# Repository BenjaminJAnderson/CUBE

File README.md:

# CUBE

CUBE is a miniature, six-faced OLED display cube built from a stack of custom interconnected PCBs. The current design combines an ESP32-S2 motherboard, five further display boards, a magnet-held 3D-printed frame and bring-up firmware for SPI displays and motion sensing.

## Overview

CUBE is a handheld, self-contained display object rather than a conventional LED matrix. Each of its six faces carries a 1.5-inch, 128×128 RGB OLED module driven by an SSD1351 controller, giving 98,304 addressable pixels across the cube. The aim is to make a small object whose faces can show independent graphics and respond to movement, while remaining easy to open, charge and repair.

The project began in December 2021 after seeing Greg Davill's [miniature LED cube](https://gregdavill.com/blog/2020/6/13/miniature-3456x-led-cube) and Pol Pla's research on [Display Blocks](https://dam-prod.media.mit.edu/x/files/sites/default/files/TEI_DisplayBlocks_CameraReady_lite.pdf). Both demonstrated the appeal of a compact, tactile display device. CUBE takes that idea in a different direction: instead of an FPGA and an LED matrix, it uses a microcontroller, six square OLED modules and a modular PCB-and-frame construction.

**Status:** design-stage prototype. The repository records work from December 2021 to May 2022. It contains the electrical and mechanical design files, photographs of a fabricated motherboard and several printed frame prototypes, and display and IMU bring-up sketches. The final assembled cube and an integrated application firmware are not present.

## Features

- **Six active faces:** one 128×128 RGB OLED on the motherboard and one on each of the five display boards.
- **Shared SPI display bus:** all six SSD1351 displays share clock, data and data/command lines, with a separate chip-select line for each face.
- **Daisy-chained construction:** 20-way, 0.5 mm pitch flat flexible cables carry power and SPI between boards, allowing the cube to be unfolded for assembly and servicing.
- **ESP32-S2 motherboard:** native USB, external-antenna module footprint, ICM-20602 six-axis IMU, USB-C input, LiPo charger with load sharing, 3.3 V regulation and a 13 V boost converter for the OLEDs.
- **Modular display boards:** D2–D6 each carry one display, two FFC connectors and the necessary decoupling and termination. The repeated design allows a single side to be revised independently later.
- **Magnet-held frame:** FreeCAD models and STEP/STL exports for the enclosure, using 3 mm neodymium magnets to join printed panels.
- **Bring-up software:** Arduino sketches that test one display at a time up to six displays, exercise the Adafruit GFX drawing primitives, and demonstrate IMU orientation output.

## Technologies

- **KiCad:** schematic capture, PCB layout and fabrication outputs. D1 uses the KiCad 6 project format; D2–D6 use the earlier `.sch` and `.pro` format.
- **ESP32-S2:** the ESP32-S2-MINI-1U supplies the processing, Wi-Fi, native USB and external-antenna option.
- **SSD1351 and Adafruit GFX:** display driver and graphics library used by the OLED modules and test sketches.
- **C/C++ with the Arduino framework:** firmware bring-up sketches for the displays and IMU.
- **FreeCAD:** mechanical design of the frame, including the panel and magnet layouts.
- **Blender:** rendered presentation of the assembled cube.
- **JLCPCB:** SLA 3D printing service used for the individual frame panels.

## Gallery

*The assembled motherboard, showing the ESP32-S2 module, USB-C connector, battery connector, FFC connector and power circuitry.*

*Motherboard schematic sheets covering the 13 V and 3.3 V supplies, battery management, USB input, IMU, display interface and ESP32-S2.*

*Mechanical reference for the 1.5-inch, 128×128 RGB OLED module, including its active area, bezel and FFC tail.*

*Two frame halves with the PCB assembly test-fitted inside.*

*An early FDM-printed frame, printed flat and folded like origami to avoid overhangs.*

*Individual SLA-printed panels with magnet pockets, produced through JLCPCB's 3D printing service.*

*A PCB and display test-fitted into a printed frame panel.*

## Technical Details

### System architecture

CUBE is built from six boards arranged as the faces of a cube. D1 is the motherboard and also carries one display. D2–D6 are display boards with the same electrical function: each accepts the incoming bus, drives one OLED and passes the bus to the next face. The boards are approximately 38 mm across and use two copper layers. The FreeCAD frame envelope is approximately 52 mm cubed.

The interconnect is a 20-way, 0.5 mm pitch FFC bus. It carries the shared SPI clock and data lines, the data/command line, 3.3 V, the 13 V OLED supply, ground and the chip-select lines that have not yet been consumed. D1 uses one select locally and forwards five to D2. Each subsequent board consumes one select and forwards the remainder, so the number of active select lines decreases along the chain until, in the intended design, D6 receives the final line. Because every display has its own chip-select, the microcontroller can update one face without disturbing the others.

### Motherboard

The motherboard is built around an ESP32-S2-MINI-1U. The module's native USB interface removes the need for a separate USB-to-UART bridge, reducing component count and board area. The 1U variant was selected for its external-antenna option.

The main subsystems are:

- **Power input and battery management:** a USB-C receptacle feeds a MCP73831 LiPo charger. A P-channel MOSFET and Schottky diode provide load sharing between USB and battery power. A 2-pin JST PH connector accepts the battery.
- **Regulation:** a MIC5353 provides the 3.3 V rail, while a FAN5331 boost converter generates the 13 V bias required by the OLED modules.
- **Sensing:** an ICM-20602 accelerometer and gyroscope share the SPI bus and provide an interrupt output.
- **Display interface:** a 20-pin FFC connector distributes the bus to the first display board. The motherboard also carries one SSD1351 display module on its top face.
- **Control and status:** a two-way DIP switch provides boot and reset control, and green LEDs indicate power and charger status.

### Display boards

D2–D6 share the same basic layout and component set, although the chip-select wiring changes along the chain. Each board contains one 1.5-inch 128×128 SSD1351 OLED module, two 20-pin FFC connectors for the daisy chain, decoupling capacitors and series components for the display signals. There is no local microcontroller; all rendering is performed by the ESP32-S2 and sent over the shared bus.

The D6 directory currently contains copies of the D5 files, including the D5 chip-select assignment. This is a known naming and versioning artefact: D6 is intended to be the sixth display face, and the duplicate was left in place so that a single side could be modified later without changing the other four. Before D6 can act as the sixth face, its netlist needs to be changed to consume only `Display6_CS`.

### Mechanical design

The enclosure was developed in FreeCAD and exported as STEP and STL files. The frame is approximately 52 mm cubed and uses 3 mm neodymium magnets to hold its sections together so that the cube can be opened for charging or repair. The repository includes the FreeCAD source, the six wall panels, a compound assembly and several earlier design iterations in `Hardware/Frame/OLD`.

Three fabrication approaches were explored:

1. **FDM-printed folded frame:** the panels were printed flat in ABS and folded like origami. This avoided overhangs and produced a smooth outer surface, but the print quality and tolerances were not good enough for a finished object.
2. **Single-piece SLA lid:** an SLA print gave a better surface finish, but the material was brittle and chipped during support removal. Placing PCBs into a frame with five connected panels was also difficult.
3. **Individual magnet panels:** each panel was printed separately through JLCPCB's SLA service, allowing the PCBs and displays to be fitted easily. The finish was the best of the three, but the resulting frame was fragile when pressure was applied to opposite corners, and gluing the many magnets was slow and error-prone.

The design direction recorded in the project notes is a final frame made from two evenly sized three-sided sections, printed in SLA, with improved magnet pockets. Keeping each section to three sides makes assembly easier while still allowing the cube to be opened.

### Firmware and bring-up

The software is a collection of Arduino sketches rather than a finished application. The sequence in `Software/Display/Testing` progresses from a single display to test routines for all six faces. `1_Display_SW` initialises one display, and the later sketches add calls for more faces. The progression is not fully consistent: `3_Display_SW` initialises OLED4 but not OLED3, while `5_Display_SW` and `6_Display_SW` call drawing routines on the fifth and sixth displays without calling `begin()` on those objects. The sketches use software SPI with the following pins:

| Signal | GPIO |
| --- | --- |
| SCLK | 36 |
| MOSI | 35 |
| DC | 5 |
| CS 1 | 6 |
| CS 2 | 12 |
| CS 3 | 14 |
| CS 4 | 18 |
| CS 5 | 17 |
| CS 6 | 11 |

The display sketches use the Adafruit GFX drawing API and the Adafruit SSD1351 driver. The vendored driver files in `Software/Display/lib` have been renamed to `Multi_SSD1351`, but the source still includes `Adafruit_SSD1351.h`; the upstream Adafruit SSD1351 library should therefore be installed when building the sketches.

The IMU sketches in `Software/IMU` use an MPU6050 and Jeff Rowberg's DMP library over I2C. They print yaw, pitch and roll over serial for orientation experiments, but they do not drive the ICM-20602 fitted to the motherboard. An ICM-20602 SPI driver and the integration between sensing, rendering and power management remain to be written.

## Challenges and Solutions

### Driving six displays from one bus

Six displays could not each have a dedicated SPI peripheral, and duplicating the bus would have added wiring and pins. The chosen approach shares clock, data and data/command lines while giving every display its own chip-select. Each board consumes one select line and passes the unused lines to the next board, so the ESP32-S2 can still address any face individually without carrying all six selects to the end of the chain. The staged one-to-six test sketches provide an incremental validation path for this arrangement.

### Sourcing a suitable square display

Small, high-resolution square OLED modules are uncommon. The available 1.5-inch 128×128 SSD1351 modules have relatively large bezels, which limits the visible area of each face. The design accepts this trade-off because the modules are readily available, have an integrated controller and use a simple SPI interface. Smaller square OLEDs may become easier to source as the VR and wearable markets grow.

### Producing a repeatable frame

Each frame process exposed a different limitation: FDM printing gave poor surface finish and tolerances, SLA printing was brittle and difficult to clean up, and individual magnet panels were fragile under diagonal loads. The current design direction is two three-sided SLA sections with improved magnet pockets, balancing print quality, ease of assembly and serviceability. The prototype frames in the repository are development iterations, not the final enclosure.

### Reducing component count

An early constraint was fitting the electronics into a small cube. The ESP32-S2's native USB removed the USB-to-UART bridge and its associated circuitry, and the ESP32-S2-MINI-1U provided the processing and wireless capability in a small module. The remaining power path was kept modular: USB-C input, a LiPo charger with load sharing, a 3.3 V rail and a dedicated 13 V boost for the displays.

## Results and Validation

The repository contains evidence of the following work:

- A fabricated D1 motherboard, photographed and shown test-fitted in a frame assembly.
- KiCad schematics and PCB layouts for the motherboard and display boards.
- Printed frame prototypes, including folded FDM frames, SLA panels and a PCB test fit.
- Staged display sketches that progress from one display to calls for six faces and exercise drawing primitives.
- An IMU orientation sketch using the MPU6050 DMP library.

There is no automated test suite, no captured frame-rate or power-consumption measurements, and no integrated application firmware in this repository. The final cube has not been assembled from the final frame design.

Known limitations:

- D6 duplicates the D5 hardware files, including the D5 chip-select wiring, and is not independently versioned.
- Several sketches omit `begin()` calls: `3_Display_SW` does not initialise OLED3, and `5_Display_SW` and `6_Display_SW` do not initialise the fifth and sixth display objects.
- The vendored SSD1351 driver is renamed but retains the upstream include name.
- The IMU sketch targets the MPU6050, while the motherboard uses the ICM-20602.
- The final two-part SLA frame and the integrated firmware are still outstanding.

## Getting Started

### Prerequisites

- KiCad 6 or newer to open the D1 project; the D2–D6 boards use the older KiCad `.sch` and `.pro` formats.
- FreeCAD to edit the enclosure source and export STEP or STL files.
- Arduino IDE or an equivalent Arduino toolchain with the ESP32 board support package for the firmware sketches.
- Adafruit GFX and Adafruit SSD1351 libraries for the display sketches.
- Jeff Rowberg's MPU6050 library for the IMU demonstration.
- Blender if you want to open the presentation render.
- For a physical build: six 1.5-inch 128×128 SSD1351 OLED modules, 20-way 0.5 mm FFC cables and connectors, a compatible LiPo battery, 3 mm neodymium magnets and the printed frame parts.

### Opening the hardware design

Open `Hardware/PCB/D1(Motherboard)/D1(Motherboard).kicad_pro` in KiCad for the motherboard. The display boards are in `Hardware/PCB/D2` through `Hardware/PCB/D6`; D6 contains a copy of the D5 project.

The schematic and layout can also be viewed online through [CADLAB.io](https://cadlab.io/project/25014).

### Running the firmware

1. Install the ESP32 board support package and the Adafruit GFX and Adafruit SSD1351 libraries in the Arduino IDE.
2. Open the desired sketch under `Software/Display/Testing`. Start with `1_Display_SW` for a single display, then move up to `6_Display_SW`.
3. Select the ESP32-S2 board that matches the module on the motherboard.
4. Check the pin definitions at the top of the sketch against the board revision before uploading. The pin assignments above reflect the test sketches, not a separate board definition.
5. Add any missing `begin()` calls (for example, OLED3 in `3_Display_SW`, and OLED5 and OLED6 in the later sketches).
6. Open the Serial Monitor to see the display initialisation and test output.

For the IMU experiment, open `Software/IMU/DMP_CodeESP32/DMP_CodeESP32.ino`, install the MPU6050 library and connect an MPU6050 over I2C. This sketch is an experiment for the MPU6050 and is not a driver for the ICM-20602 on the motherboard.

### Frame and renders

The editable frame source is `Hardware/Frame/Frame.FCStd`. Exports include `Frame-Walls.step`, `Frame-Left.step`, `Frame-Compound002.step` and `Frame-Walls.stl`. Earlier frame versions are kept in `Hardware/Frame/OLD`.

The Blender presentation file is `Renders/Blender/Cube Render.blend`.

## Project Structure

```text
CUBE/
├── Hardware/
│   ├── PCB/
│   │   ├── D1(Motherboard)/    # Motherboard, power, IMU and display interface
│   │   ├── D2/                 # Display board
│   │   ├── D3/                 # Display board
│   │   ├── D4/                 # Display board
│   │   ├── D5/                 # Display board
│   │   └── D6/                 # Sixth display face; currently a copy of D5
│   └── Frame/                  # FreeCAD source, STEP exports and STL files
├── Renders/
│   ├── Blender/                # Blender presentation scene
│   ├── CubeDesign.png          # High-resolution render
│   └── Test.png                # Render
├── Software/
│   ├── Display/                # SSD1351 libraries, examples and bring-up tests
│   └── IMU/                    # MPU6050 DMP experiments
├── docs/images/                # README images
├── LICENSE
└── README.md
```

## Roadmap

- [ ] Finalise the enclosure as two three-sided SLA-printed sections with improved magnet pockets.
- [ ] Assemble a complete six-face cube from the final frame and boards.
- [ ] Write and document integrated application firmware for rendering, motion sensing and power management.
- [ ] Add an ICM-20602 SPI driver and connect it to the display application.
- [ ] Allow individual display-board revisions for each face; D6 remains a duplicate for now.

## Credits and Licensing

The project source and design files are released under the [MIT License](LICENSE), copyright 2022 Benjamin J Anderson.

Third-party material:

- The display driver and graphics code derive from Adafruit's SSD1351 and GFX libraries, which are distributed under the BSD licence. The original SSD1351 library and its licence are included in `Software/Display/Resources/Adafruit-SSD1351-library-1.1.0`.
- The IMU sketches depend on Jeff Rowberg's I2Cdevlib MPU6050 library, which is not bundled in this repository.
- Reference sketches in `Software/Display/Resources` include material from the Rotatey_Balls project, distributed under the MIT licence.
- Component datasheets, antenna documentation and vendor reference designs in `Hardware/PCB/D1(Motherboard)/Resources` remain subject to their publishers' terms.
- Design inspiration: Greg Davill's miniature LED cube and Pol Pla's Display Blocks research, linked in the Overview.

The project is also indexed on [CADLAB.io](https://cadlab.io/project/25014).

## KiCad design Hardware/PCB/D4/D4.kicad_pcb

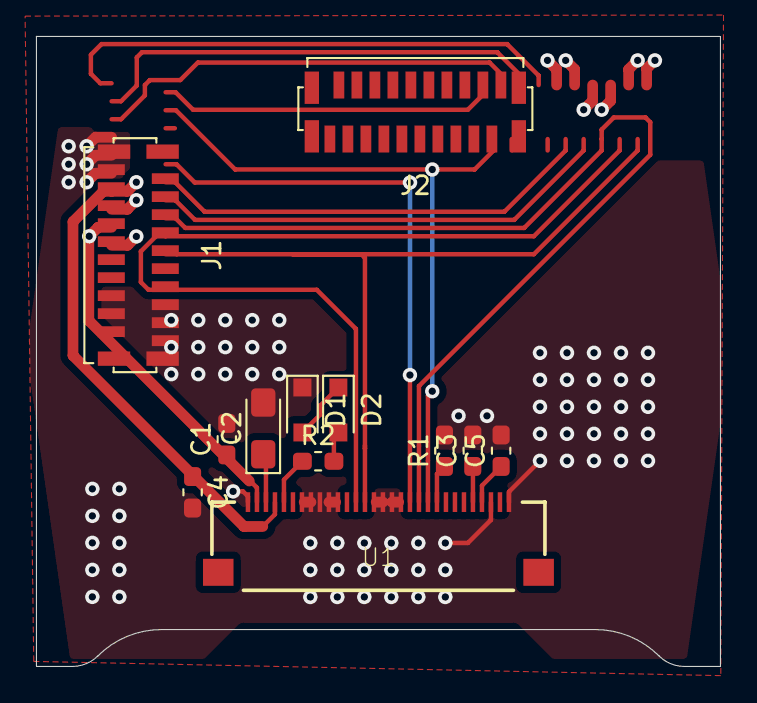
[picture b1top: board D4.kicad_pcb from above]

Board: 2 copper layers, 38.0 x 35.0 mm, 12 parts (0 on the bottom side), 21 nets.

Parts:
C1, C5: 10u; C_0603_1608Metric_Pad1.05x0.95mm_HandSolder
C2: 4.7u; CP_EIA-3216-18_Kemet-A_Pad1.58x1.35mm_HandSolder
C3: 0.1u; C_0603_1608Metric_Pad1.05x0.95mm_HandSolder
C4: 1u; C_0603_1608Metric_Pad1.05x0.95mm_HandSolder
D1, D2: 1N4148; D_SOD-323_HandSoldering
J1, J2: Conn_01x20_Female; FH12-20S-0.5SVA
R1: 560k; R_0603_1608Metric_Pad1.05x0.95mm_HandSolder
R2: 50R; R_0603_1608Metric_Pad1.05x0.95mm_HandSolder
U1: 4DOLED-282815; FPC_XF2M-3015-1A

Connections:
13V: C1.1, J1.17, J1.19, J2.1, J2.3, U1.2
+3V3: C4.1, J1.13, J1.15, J2.5, J2.7, U1.4
CLK: J1.20, J2.2, U1.14
DC: J1.16, J2.6, U1.20
Display4_CS: J1.10, U1.19
Display5_CS: J1.12, J2.10
Display6_CS: J1.14, J2.8
EN: J1.5, J2.17
GND: C1.2, C2.2, C3.2, C4.2, C5.2, D1.1, J1.7, J1.9, J1.11, J2.9, J2.11, R1.2, U1.1, U1.7, U1.8, U1.9, U1.10, U1.11, U1.15, U1.16, U1.17, U1.18, U1.28, U1.30
IO0: J1.3, J2.15
MOSI: J1.18, J2.4, U1.13
unnamed: C2.1, U1.3
unnamed: C3.1, U1.26
unnamed: C5.1, U1.27
unnamed: D1.2, D2.1
unnamed: D2.2, R2.2
unnamed: R1.1, U1.22
unnamed: R2.1, U1.5
RST: J1.4, J2.18, U1.21
RXD: J1.1, J2.13
TXD: J1.2, J2.19

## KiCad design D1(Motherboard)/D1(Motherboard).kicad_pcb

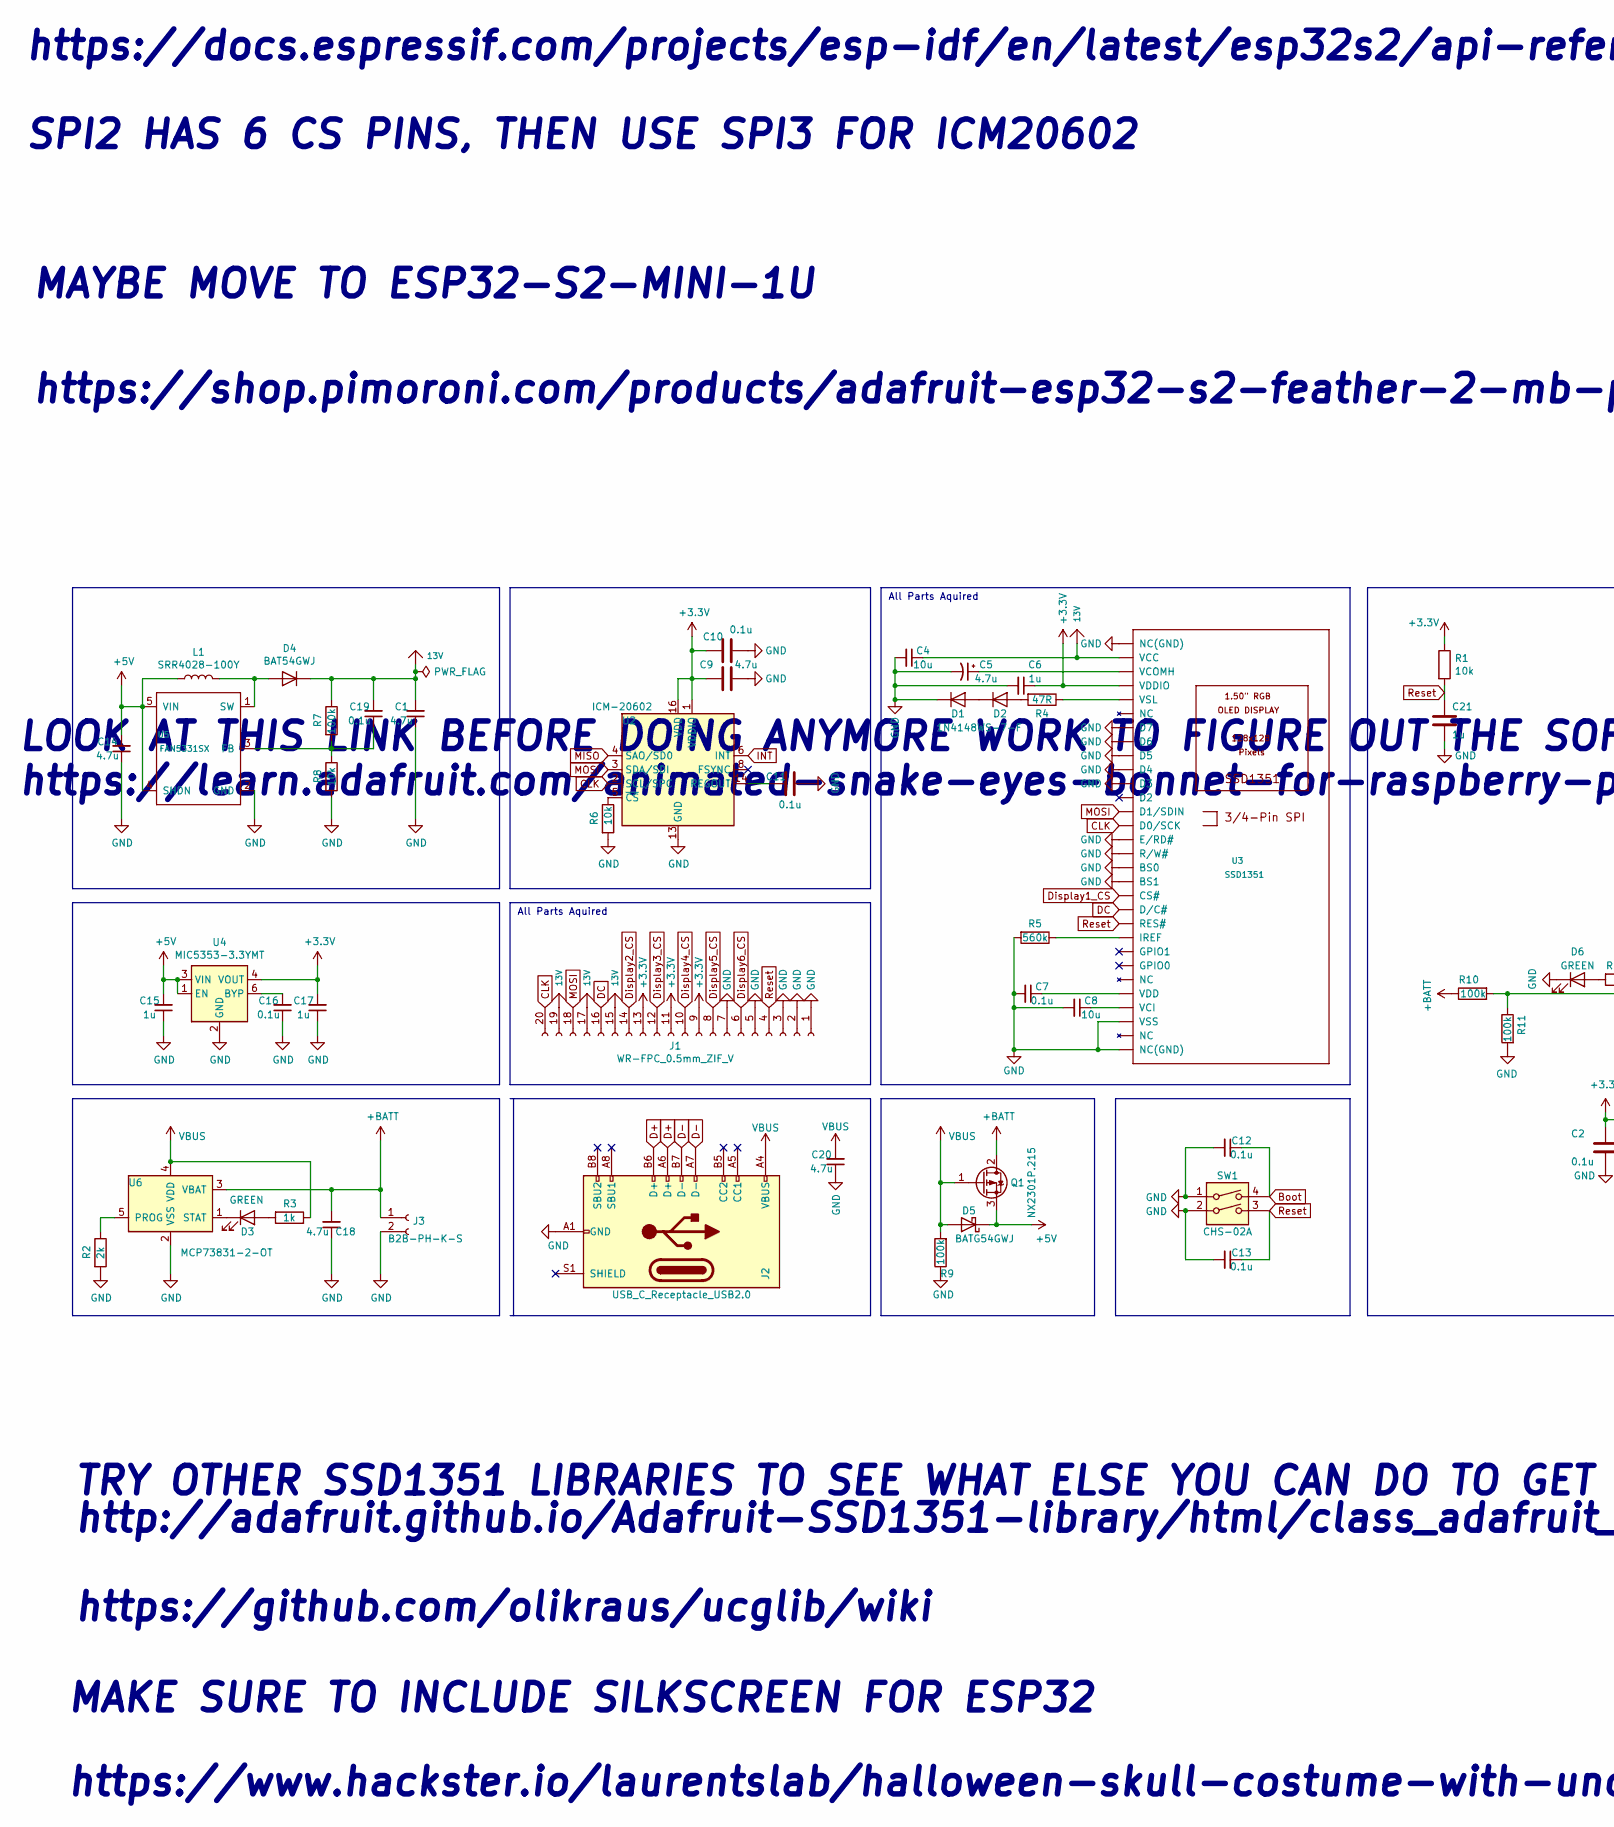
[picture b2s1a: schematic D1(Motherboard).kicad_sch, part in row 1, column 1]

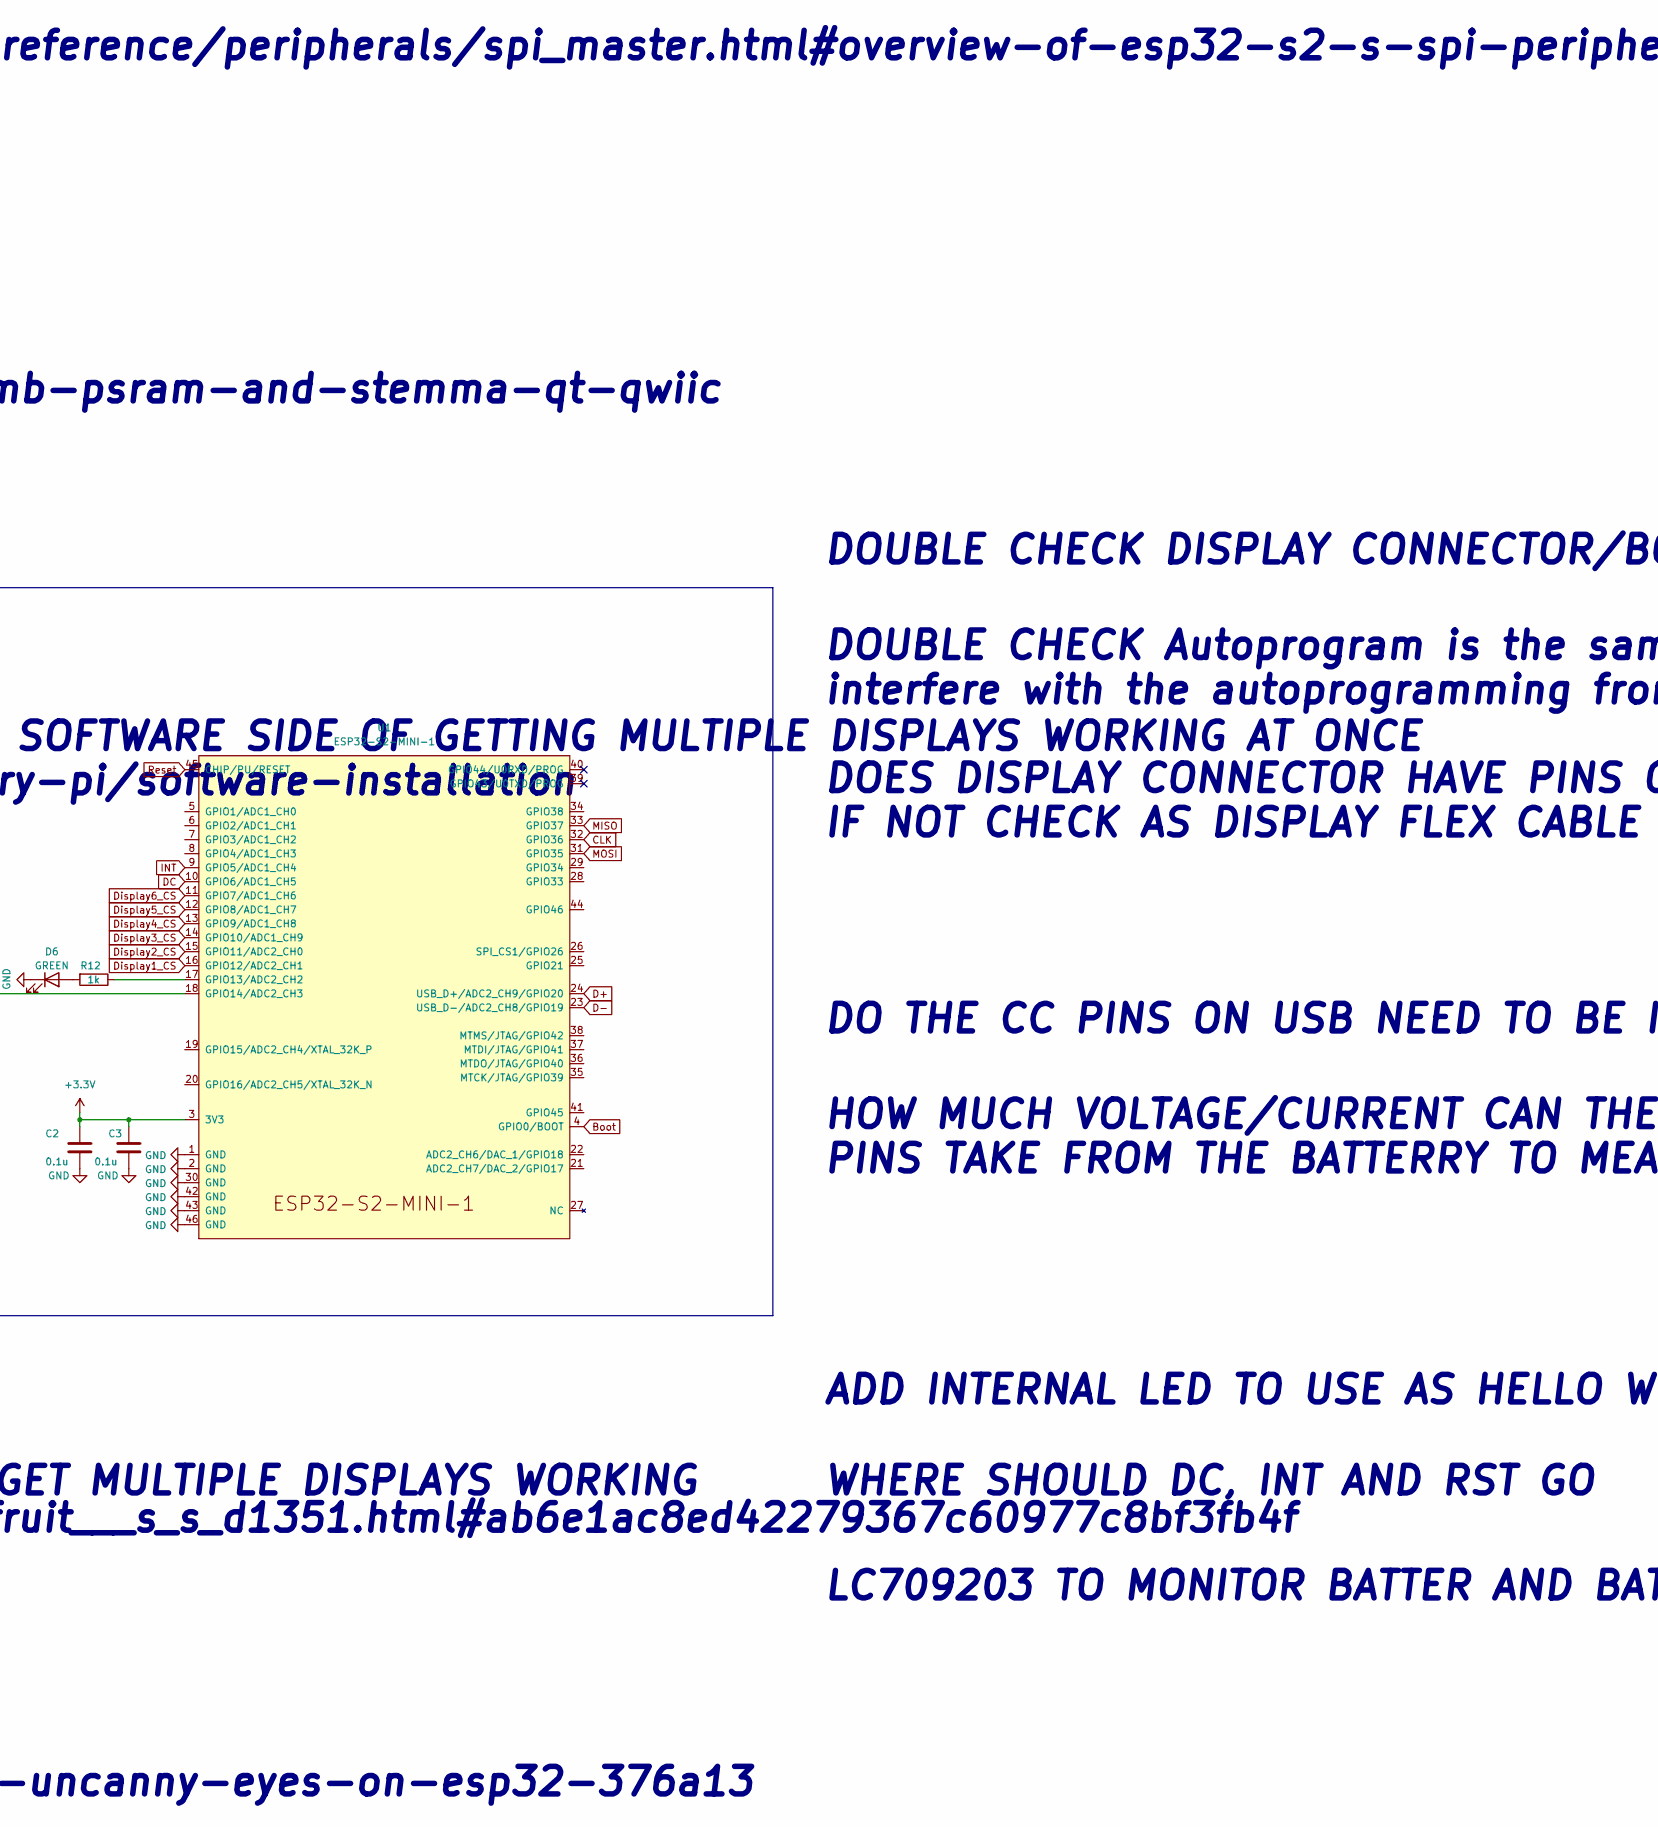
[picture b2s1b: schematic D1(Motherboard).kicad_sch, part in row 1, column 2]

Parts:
C1, C9, C14, C18, C20: 4.7u; C_0603_1608Metric
C2, C3, C7, C10, C11, C12, C13, C16, C19: 0.1u; C_0603_1608Metric
C4, C8: 10u; C_0603_1608Metric
C5: 4.7u; CP_EIA-3216-18_Kemet-A
C6, C15, C17, C21: 1u; C_0603_1608Metric
D1, D2: 1N4148WS-7-F; D_SOD-323
D3, D6: GREEN; LED_0603_1608Metric
D4: BAT54GWJ; D_SOD-123
D5: BATG54GWJ; D_SOD-123
J1: WR-FPC_0.5mm_ZIF_V; WR-FPC_0.50_SMT_ZIF_V
J2: USB_C_Receptacle_USB2.0; GCT_USB4120-03-C
J3: B2B-PH-K-S; JST_PH_B2B-PH-K_1x02_P2.00mm_Vertical
L1: SRR4028-100Y; L_Bourns-SRN4028
Q1: NX2301P.215; SOT-23
R1, R6, R8: 10k; R_0603_1608Metric
R2: 2k; R_0603_1608Metric
R3, R12: 1k; R_0603_1608Metric
R4: 47R; R_0603_1608Metric
R5: 560k; R_0603_1608Metric
R7, R9, R10, R11: 100k; R_0603_1608Metric
SW1: CHS-02A; SW_DIP_SPSTx02_Slide_Copal_CHS-02A_W5.08mm_P1.27mm_JPin
U1: ESP32-S2-MINI-1; ESP32-S2-MINI-1U
U2: ICM-20602; LGA-16_3x3mm_P0.5mm_LayoutBorder3x5y
U3: SSD1351; WR-FPC_0.5mm_ZIF_H
U4: MIC5353-3.3YMT; MLF-6-1EP_1.6x1.6mm_P0.5mm_EP0.5x1.26mm
U5: FAN5331SX; SOT-23-5
U6: MCP73831-2-OT; SOT-23-5

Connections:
13V: C1.2, C4.1, C19.2, D4.1 (K), J1.15, J1.17, J1.19, R7.1, U3.2 (VCC)
+3V3: C2.1, C3.1, C6.1, C9.2, C10.2, C17.2, J1.9, J1.11, J1.13, R1.1, U1.3 (3V3), U2.1 (VDDIO), U2.16 (VDD), U3.4 (VDDIO), U4.4 (VOUT)
+5V: C14.2, C15.2, D5.1 (K), L1.1, Q1.3 (S), U4.1 (EN), U4.3 (VIN), U5.4 (SHDN), U5.5 (VIN)
+BATT: C18.2, J3.1, Q1.2 (D), R10.1, U6.3 (VBAT)
Boot: C12.1, SW1.4, U1.4 (GPIO0/BOOT)
CLK: J1.20, U1.32 (GPIO36), U2.2 (SCL/SPC), U3.14 (D0/SCK)
D+: J2.A6 (D+), J2.B6 (D+), U1.24 (USB_D+/ADC2_CH9/GPIO20)
D-: J2.A7 (D-), J2.B7 (D-), U1.23 (USB_D-/ADC2_CH8/GPIO19)
DC: J1.16, U1.10 (GPIO6/ADC1_CH5), U3.20 (D/C#)
Display1_CS: U1.16 (GPIO12/ADC2_CH1), U3.19 (CS#)
Display2_CS: J1.14, U1.15 (GPIO11/ADC2_CH0)
Display3_CS: J1.12, U1.14 (GPIO10/ADC1_CH9)
Display4_CS: J1.10, U1.13 (GPIO9/ADC1_CH8)
Display5_CS: J1.8, U1.12 (GPIO8/ADC1_CH7)
Display6_CS: J1.6, U1.11 (GPIO7/ADC1_CH6)
GND: C1.1, C2.2, C3.2, C4.2, C5.2, C6.2, C7.2, C8.2, C9.1, C10.1, C11.1, C12.2, C13.2, C14.1, C15.1, C16.1, C17.1, C18.1, C20.1, C21.2, D1.1 (K), D6.1 (K), J1.1, J1.2, J1.3, J1.5, J1.7, J2.A1 (GND), J2.A12 (GND), J2.B1 (GND), J2.B12 (GND), J3.2, R2.2, R5.2, R6.2, R8.2, R9.1, R11.2, SW1.1, SW1.2, U1.1 (GND), U1.2 (GND), U1.30 (GND), U1.42 (GND), U1.43 (GND), U1.46 (GND), U2.9 (GND), U2.10 (GND), U2.11 (GND), U2.12 (GND), U2.13 (GND), U2.15 (GND), U3.1 (NC(GND)), U3.7 (D7), U3.8 (D6), U3.9 (D5), U3.10 (D4), U3.11 (D3), U3.15 (E/RD#), U3.16 (R/W#), U3.17 (BS0), U3.18 (BS1), U3.28 (VSS), U3.30 (NC(GND)), U4.2 (GND), U4.7 (GND), U5.2 (GND), U6.2 (VSS)
INT: U1.9 (GPIO5/ADC1_CH4), U2.6 (INT)
MISO: U1.33 (GPIO37), U2.4 (SAO/SD0)
MOSI: J1.18, U1.31 (GPIO35), U2.3 (SDA/SDI), U3.13 (D1/SDIN)
unnamed: C5.1, U3.3 (VCOMH)
unnamed: C7.1, U3.26 (VDD)
unnamed: C8.1, U3.27 (VCI)
unnamed: C11.2, U2.14 (REGOUT)
unnamed: C16.2, U4.6 (BYP)
unnamed: C19.1, R7.2, R8.1, U5.3 (FB)
unnamed: D1.2 (A), D2.1 (K)
unnamed: D2.2 (A), R4.2
unnamed: D3.1 (K), U6.1 (STAT)
unnamed: D3.2 (A), R3.2
unnamed: D4.2 (A), L1.2, U5.1 (SW)
unnamed: D6.2 (A), R12.2
unnamed: R2.1, U6.5 (PROG)
unnamed: R4.1, U3.5 (VSL)
unnamed: R5.1, U3.22 (IREF)
unnamed: R6.1, U2.5 (~CS)
unnamed: R10.2, R11.1, U1.18 (GPIO14/ADC2_CH3)
unnamed: R12.1, U1.17 (GPIO13/ADC2_CH2)
Reset: C13.1, C21.1, J1.4, R1.2, SW1.3, U1.45 (CHIP/PU/RESET), U3.21 (RES#)
VBUS: C20.2, D5.2 (A), J2.A4 (VBUS), J2.A9 (VBUS), J2.B4 (VBUS), J2.B9 (VBUS), Q1.1 (G), R3.1, R9.2, U6.4 (VDD)

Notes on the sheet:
WHERE SHOULD DC, INT AND RST GO
DOES DISPLAY CONNECTOR HAVE PINS ON BOTH TOP AND BOTTOM, IF NOT CHECK AS DISPLAY FLEX CABLE IS FACING UP
TRY OTHER SSD1351 LIBRARIES TO SEE WHAT ELSE YOU CAN DO TO GET MULTIPLE DISPLAYS WORKING
DOUBLE CHECK Autoprogram is the same as one on ESP32 Devboard, where the buttons dont interfere with the autoprogramming from the usb
https://shop.pimoroni.com/products/adafruit-esp32-s2-feather-2-mb-psram-and-stemma-qt-qwiic
MAKE SURE TO INCLUDE SILKSCREEN FOR ESP32
LOOK AT THIS LINK BEFORE DOING ANYMORE WORK TO FIGURE OUT THE SOFTWARE SIDE OF GETTING MULTIPLE DISPLAYS WORKING AT ONCE https://learn.adafruit.com/animated-snake-eyes-bonnet-for-raspberry-pi/software-installation
https://www.hackster.io/laurentslab/halloween-skull-costume-with-uncanny-eyes-on-esp32-376a13
LC709203 TO MONITOR BATTER AND BATTERY PERCENTAGE. IT CAN BE USED OVER I2C
All Parts Aquired
HOW MUCH VOLTAGE/CURRENT CAN THE ANALOG PINS TAKE FROM THE BATTERRY TO MEASURE CAPACITY
DOUBLE CHECK DISPLAY CONNECTOR/BOARD CONNECTORS ARE CORRECT
http://adafruit.github.io/Adafruit-SSD1351-library/html/class_adafruit___s_s_d1351.html#ab6e1ac8ed42279367c60977c8bf3fb4f https://github.com/olikraus/ucglib/wiki
ADD INTERNAL LED TO USE AS HELLO WORLD
MAYBE MOVE TO ESP32-S2-MINI-1U
DO THE CC PINS ON USB NEED TO BE INCLUDED?
https://docs.espressif.com/projects/esp-idf/en/latest/esp32s2/api-reference/peripherals/spi_master.html#overview-of-esp32-s2-s-spi-peripherals SPI2 HAS 6 CS PINS, THEN USE SPI3 FOR ICM20602

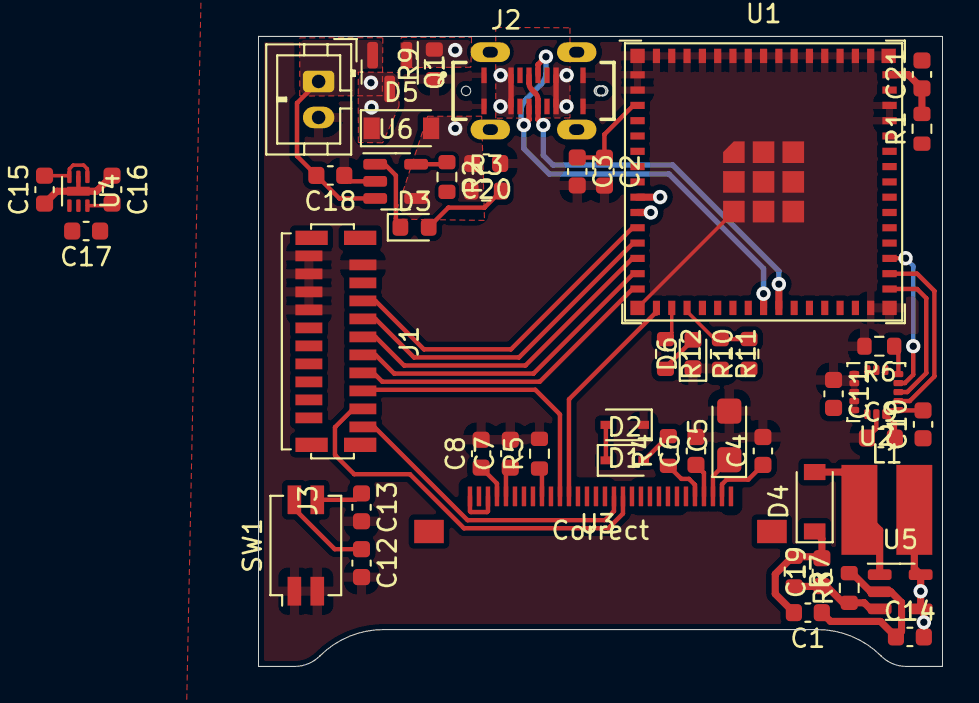
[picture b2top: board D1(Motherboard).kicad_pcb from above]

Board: 4 copper layers, 38.0 x 35.0 mm, 51 parts (0 on the bottom side), 39 nets.

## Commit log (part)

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2021-12-15 Backlink to CADLAB.io has been added.
2021-12-15 Added all KiCAD files
2021-12-15 Test Commit for CADLAB
2022-01-08 Changed to KiCAD 6
2022-01-08 Removed old Kicad filetypes from 5.0
2022-01-13 Test
2022-01-13 Upload New Version from USB
2022-01-16 Cleaned up files and organised things into folders
2022-01-16 Cleaned a bit more
2022-01-17 Added ESP32 Datasheets to recources, started cleaning up layout for esp32
2022-01-17 Changed VDD to VBUS to match other references
2022-01-17 Small update moving load sharing circuit, need to check voltage references
2022-01-18 Made paths to resources folder relative to D1 (Motherboard)
2022-01-18 Included in last commit
2022-01-19 Added antenna from ignion and changed to esp32-s2
2022-01-21 Test Commit from work computer
2022-01-21 Fixed ignion antenna, and added some more to the esp32-s2 schematic
2022-01-21 Added Flash memory, is it worth adding PSRAM???
2022-01-21 Sorted out antenna + setout loctions in corner
2022-01-22 Fixed 3D Models etc, and added to schematics + PCB
2022-01-23 More PCB work
2022-01-24 Changed antenna symbol and removed ground from pin + more layout
2022-01-25 Potentially move over to ESP32-S2-MINI-1U
2022-01-25 Looking into moving to Mini Modulate and copying adafruit schematic
2022-01-25 Continued
2022-01-25 Made changed to layout to match available space with S2 Mini 1U
2022-01-26 More layout work
2022-01-26 CHECK SOFTWARE OF MULTIPLE SPI DEVICES FIRST
2022-01-27 Some possible links to solutions
2022-01-28 Add silkscreen to ESP32
2022-01-28 Finished rough layout
2022-01-28 More Layout
2022-01-29 Test Commit
2022-01-29 Almost finished alyout and added links to look at
2022-05-25 Reformed file structure and included Freecad & software into project

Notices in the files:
README.md:
Credits and Licensing:
The project source and design files are released under the [MIT License](LICENSE), copyright 2022 Benjamin J Anderson.
Third-party material:
- The display driver and graphics code derive from Adafruit's SSD1351 and GFX libraries, which are distributed under the BSD licence. The original SSD1351 library and its licence are included in `Software/Display/Resources/Adafruit-SSD1351-library-1.1.0`.
- The IMU sketches depend on Jeff Rowberg's I2Cdevlib MPU6050 library, which is not bundled in this repository.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
